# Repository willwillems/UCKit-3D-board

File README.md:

# UCKit-3D board

KiCAD files for the 3D-UC board.

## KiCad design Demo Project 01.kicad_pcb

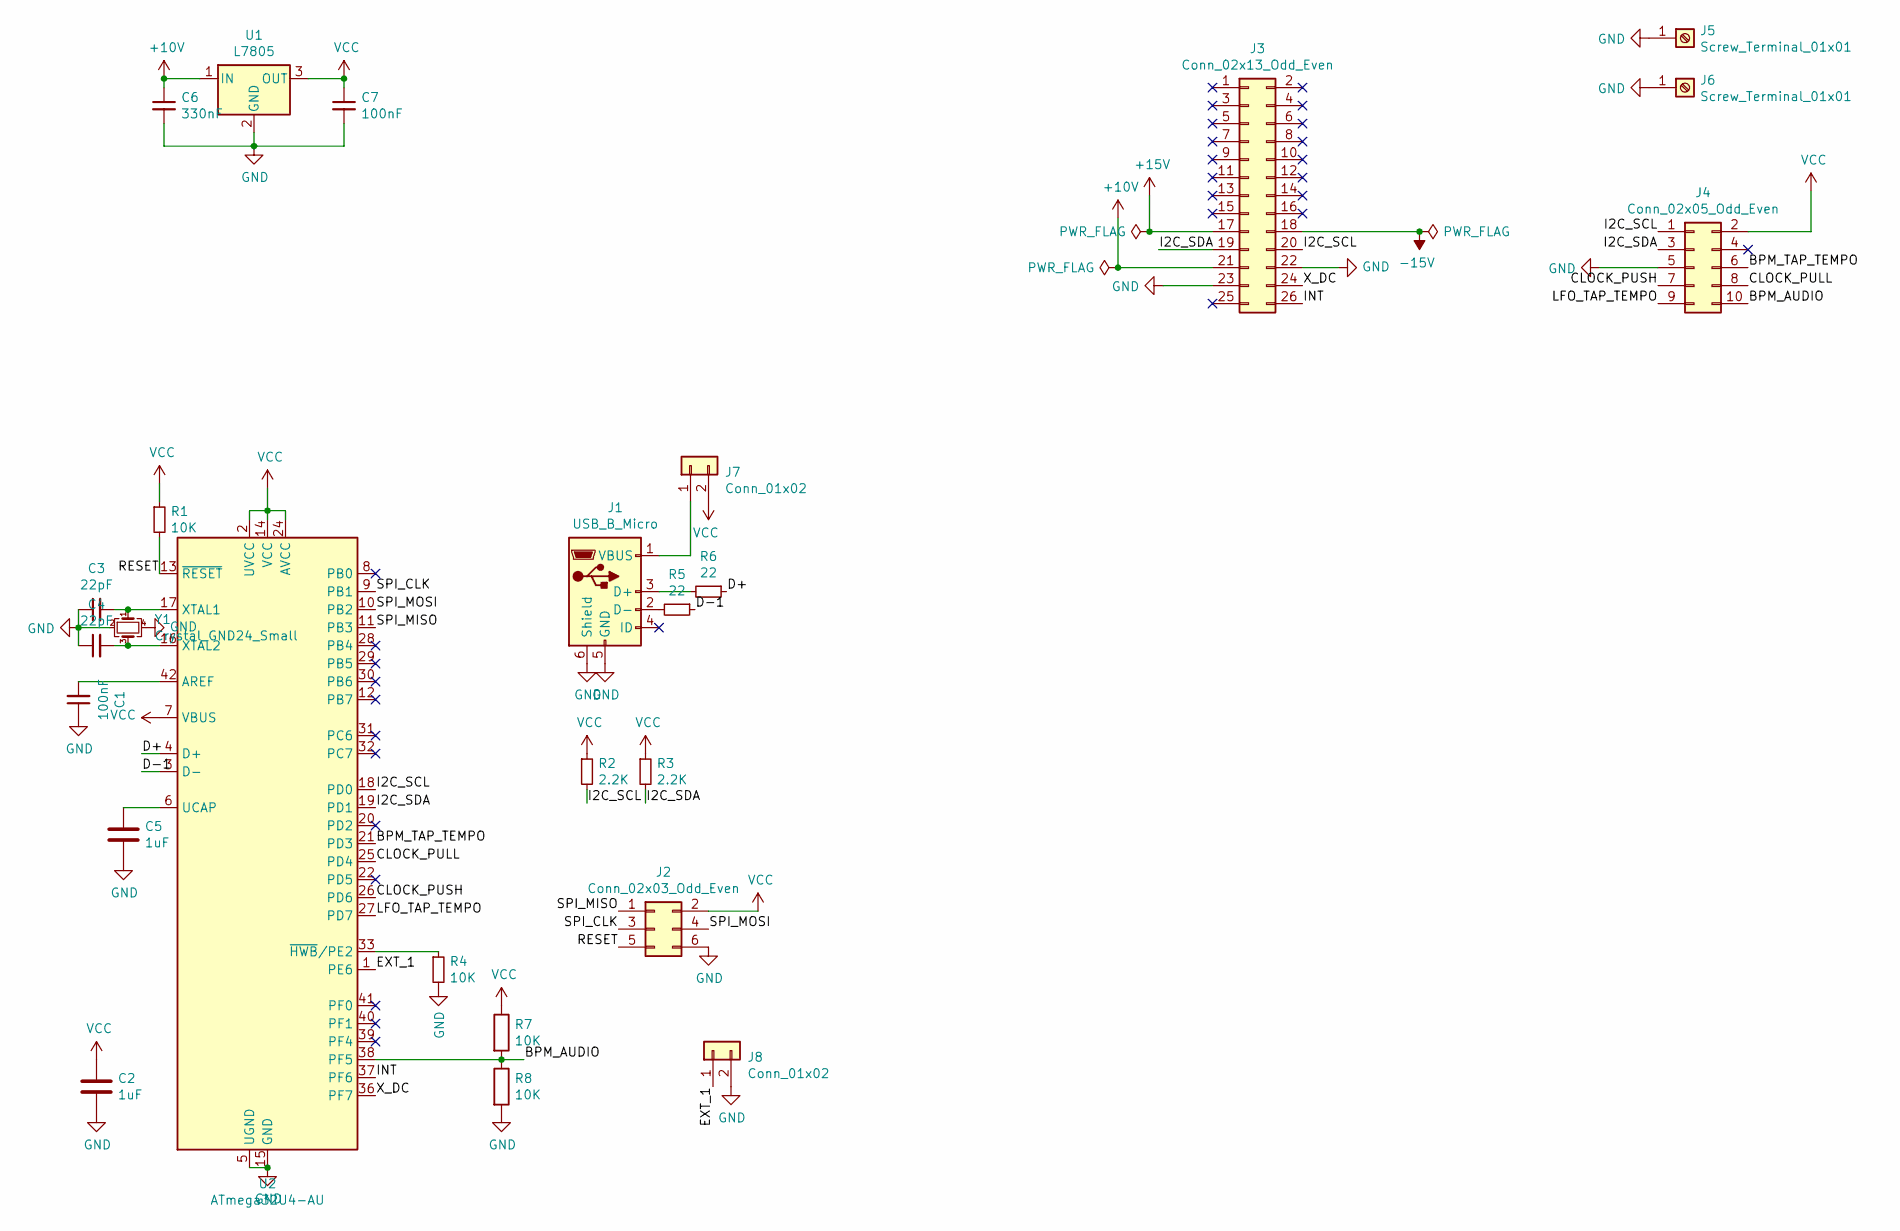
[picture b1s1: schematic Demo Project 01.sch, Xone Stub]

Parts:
C1, C7: 100nF; C_0603_1608Metric
C2, C5: 1uF; C_0603_1608Metric
C3, C4: 22pF; C_0603_1608Metric
C6: 330nF; C_0603_1608Metric
J1: USB_B_Micro; USB_Micro-B_Molex_47346-0001
J2: Conn_02x03_Odd_Even; PinHeader_2x03_P2.54mm_Vertical
J3: Conn_02x13_Odd_Even; PinHeader_2x13_P2.54mm_Vertical
J4: Conn_02x05_Odd_Even; IDC-Header_2x05_P2.54mm_Horizontal
J5, J6: Screw_Terminal_01x01; MountingHole_3.2mm_M3_Pad_Via
J7, J8: Conn_01x02; PinHeader_1x02_P2.54mm_Vertical
R1, R4, R7, R8: 10K; R_0603_1608Metric
R2, R3: 2.2K; R_0603_1608Metric
R5, R6: 22; R_0603_1608Metric
U1: L7805; TO-263-2
U2: ATmega32U4-AU; TQFP-44_10x10mm_P0.8mm
Y1: Crystal_GND24_Small; Crystal_SMD_3225-4Pin_3.2x2.5mm

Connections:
+10V: C6.1, J3.21, U1.1 (IN)
+15V: J3.17
-15V: J3.18
/BPM_AUDIO: J4.10, R7.2, R8.1, U2.38 (PF5)
/BPM_TAP_TEMPO: J4.6, U2.21 (PD3)
/CLOCK_PULL: J4.8, U2.25 (PD4)
/CLOCK_PUSH: J4.7, U2.26 (PD6)
/D+: R6.1, U2.4 (D+)
/D-1: R5.1, U2.3 (D-)
/EXT_1: J8.1, U2.1 (PE6)
/I2C_SCL: J3.20, J4.1, R2.2, U2.18 (PD0)
/I2C_SDA: J3.19, J4.3, R3.2, U2.19 (PD1)
/INT: J3.26, U2.37 (PF6)
/LFO_TAP_TEMPO: J4.9, U2.27 (PD7)
/RESET: J2.5, R1.2, U2.13 (~RESET)
/SPI_CLK: J2.3, U2.9 (PB1)
/SPI_MISO: J2.1, U2.11 (PB3)
/SPI_MOSI: J2.4, U2.10 (PB2)
/X_DC: J3.24, U2.36 (PF7)
GND: C1.1, C2.2, C3.1, C4.1, C5.2, C6.2, C7.2, J1.5 (GND), J1.6 (Shield), J2.6, J3.22, J3.23, J4.5, J5.1, J6.1, J8.2, R4.2, R8.2, U1.2 (GND), U2.5 (UGND), U2.15 (GND), U2.23 (GND), U2.35 (GND), U2.43 (GND), Y1.2, Y1.4
unnamed: C1.2, U2.42 (AREF)
unnamed: C3.2, U2.17 (XTAL1), Y1.1
unnamed: C4.2, U2.16 (XTAL2), Y1.3
unnamed: C5.1, U2.6 (UCAP)
unnamed: J1.1 (VBUS), J7.1
unnamed: J1.2 (D-), R5.2
unnamed: J1.3 (D+), R6.2
unnamed: R4.1, U2.33 (~HWB~/PE2)
VCC: C2.1, C7.1, J2.2, J4.2, J7.2, R1.1, R2.1, R3.1, R7.1, U1.3 (OUT), U2.2 (UVCC), U2.7 (VBUS), U2.14 (VCC), U2.24 (AVCC), U2.34 (VCC), U2.44 (AVCC)

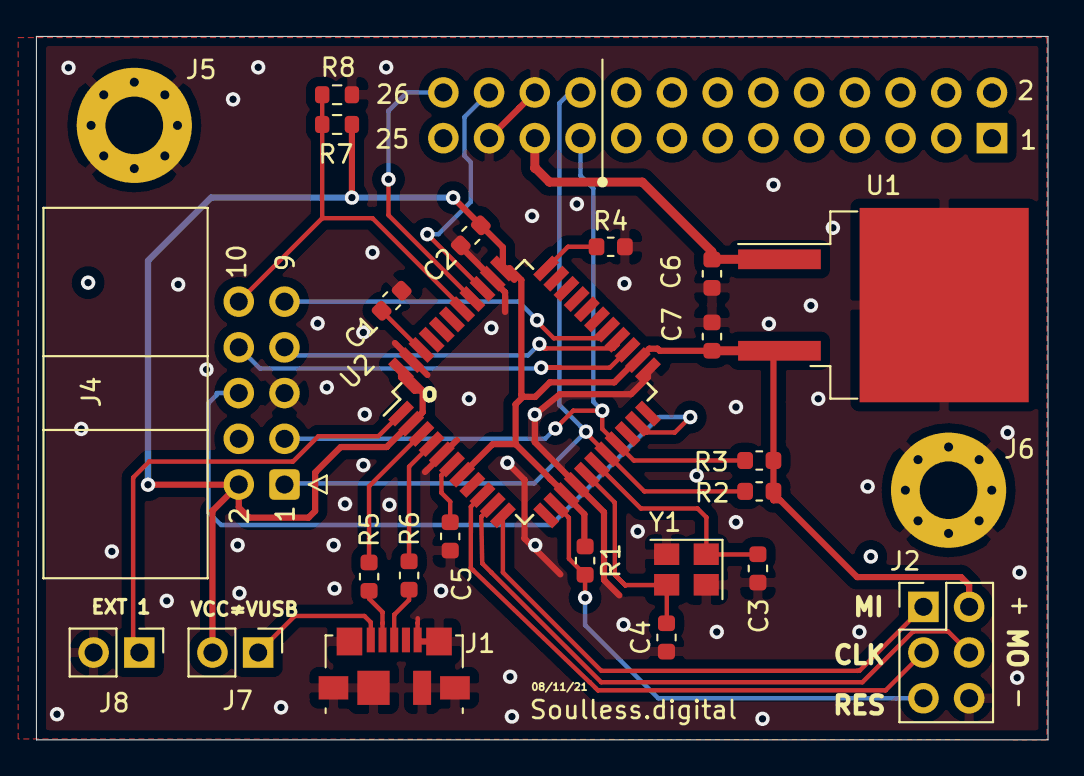
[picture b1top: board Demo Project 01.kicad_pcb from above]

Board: 2 copper layers, 56.2 x 39.1 mm, 26 parts (1 on the bottom side), 27 nets.

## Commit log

2021-12-15 git init
